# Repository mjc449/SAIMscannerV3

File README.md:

# SAIMscannerV3

Check out the preprint at https://doi.org/10.1101/533349 for more details

This project has been developed in house by the Paszek and Zipfel labs
at Cornell University over a few years and several revisions.  The
primary developer has been Marshall Colville (mjc449@cornell.edu) with
assistance from Warren Zipfel and Matt Paszek.

Given the scope of the project, the multiple revisions and adaptations
that the hardware and software have gone through, and the fact that
we are not electrical or software engineers the code tends to change
styles and not follow typical conventions.  As the project evolves we
intend to bring everything into line with a single, consistent set of
coding guidelines.  However, to go through the entire project will take
some time.  We will publish a set of style guides soon to be used throughout
the project that reflects typical coding conventions.

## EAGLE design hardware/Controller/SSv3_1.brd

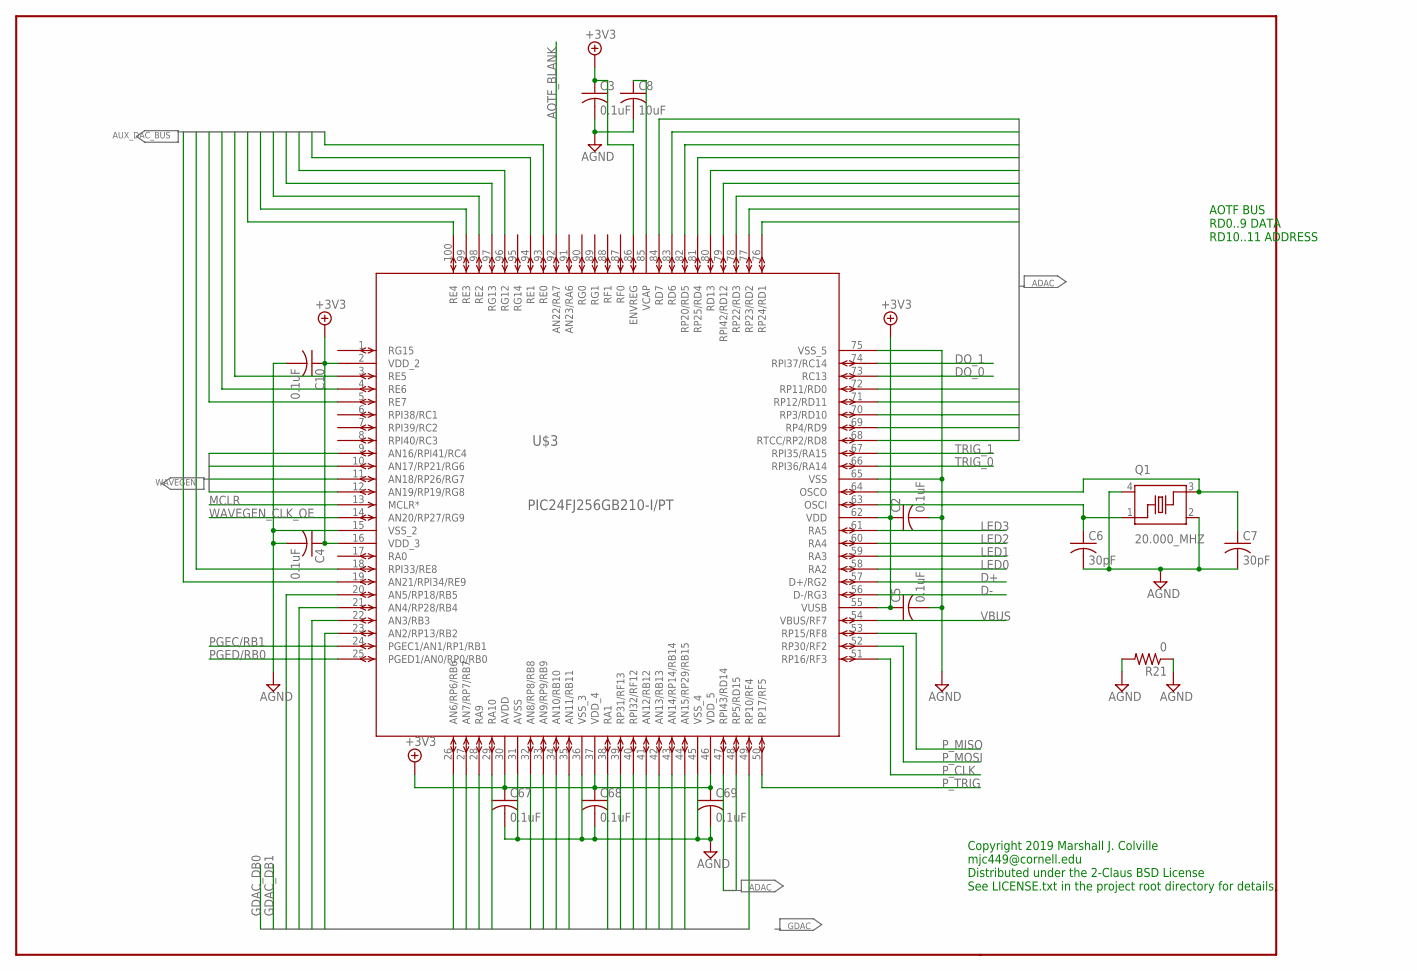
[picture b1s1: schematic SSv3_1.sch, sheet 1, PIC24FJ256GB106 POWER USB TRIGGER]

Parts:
C2, C3, C4, C5, C10, C67, C68, C69: 0.1uF; C0603
C6, C7: 30pF; C0603
C8: 10uF; C0805
Q1: 20.000_MHZ; CTS406
R21: 0; R0603
U$3: PIC24FJ256GB210-I/PT; TQFP100_12X12MC

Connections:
+3V3: C2.1, C3.1, C4.1, C5.1, C10.1, C67.1, C68.1, C69.1, U$3.2 (VDD_2), U$3.16 (VDD_3), U$3.30 (AVDD), U$3.37 (VDD_4), U$3.46 (VDD_5), U$3.55 (VUSB), U$3.62 (VDD), U$3.86 (ENVREG); also elsewhere on the board
ADAC0: U$3.72 (RP11/RD0); also elsewhere on the board
ADAC0_CS: U$3.79 (RPI42/RD12); also elsewhere on the board
ADAC1: U$3.76 (RP24/RD1); also elsewhere on the board
ADAC1_CS: U$3.80 (RD13); also elsewhere on the board
ADAC2: U$3.77 (RP23/RD2); also elsewhere on the board
ADAC3: U$3.78 (RP22/RD3); also elsewhere on the board
ADAC4: U$3.81 (RP25/RD4); also elsewhere on the board
ADAC5: U$3.82 (RP20/RD5); also elsewhere on the board
ADAC6: U$3.83 (RD6); also elsewhere on the board
ADAC7: U$3.84 (RD7); also elsewhere on the board
ADAC8: U$3.68 (RTCC/RP2/RD8); also elsewhere on the board
ADAC9: U$3.69 (RP4/RD9); also elsewhere on the board
ADAC_A0: U$3.70 (RP3/RD10); also elsewhere on the board
ADAC_A1: U$3.71 (RP12/RD11); also elsewhere on the board
ADAC_LOAD: U$3.47 (RPI43/RD14); also elsewhere on the board
ADAC_RS: U$3.48 (RP5/RD15); also elsewhere on the board
AGND: C2.2, C3.2, C4.2, C5.2, C6.2, C7.2, C8.2, C10.2, C67.2, C68.2, C69.2, Q1.2, Q1.4, R21.1, R21.2, U$3.15 (VSS_2), U$3.31 (AVSS), U$3.36 (VSS_3), U$3.45 (VSS_4), U$3.65 (VSS), U$3.75 (VSS_5); also elsewhere on the board
AOTF_BLANK: U$3.92 (AN22/RA7); also elsewhere on the board
AUX_DAC_A/B: U$3.97 (RG13); also elsewhere on the board
AUX_DAC_CS: U$3.96 (RG12); also elsewhere on the board
AUX_DAC_DB0: U$3.93 (RE0); also elsewhere on the board
AUX_DAC_DB1: U$3.94 (RE1); also elsewhere on the board
AUX_DAC_DB2: U$3.98 (RE2); also elsewhere on the board
AUX_DAC_DB3: U$3.99 (RE3); also elsewhere on the board
AUX_DAC_DB4: U$3.100 (RE4); also elsewhere on the board
AUX_DAC_DB5: U$3.3 (RE5); also elsewhere on the board
AUX_DAC_DB6: U$3.4 (RE6); also elsewhere on the board
AUX_DAC_DB7: U$3.5 (RE7); also elsewhere on the board
AUX_DAC_DB8: U$3.18 (RPI33/RE8); also elsewhere on the board
AUX_DAC_DB9: U$3.19 (AN21/RPI34/RE9); also elsewhere on the board
D+: U$3.57 (D+/RG2); also elsewhere on the board
D-: U$3.56 (D-/RG3); also elsewhere on the board
DO_0: U$3.73 (RC13); also elsewhere on the board
DO_1: U$3.74 (RPI37/RC14); also elsewhere on the board
GDAC_A0: U$3.28 (RA9); also elsewhere on the board
GDAC_A1: U$3.29 (RA10); also elsewhere on the board
GDAC_DB2: U$3.23 (AN2/RP13/RB2); also elsewhere on the board
GDAC_DB3: U$3.22 (AN3/RB3); also elsewhere on the board
GDAC_DB4: U$3.21 (AN4/RP28/RB4); also elsewhere on the board
GDAC_DB5: U$3.20 (AN5/RP18/RB5); also elsewhere on the board
GDAC_DB6: U$3.26 (AN6/RP6/RB6); also elsewhere on the board
GDAC_DB7: U$3.27 (AN7/RP7/RB7); also elsewhere on the board
GDAC_DB8: U$3.32 (AN8/RP8/RB8); also elsewhere on the board
GDAC_DB9: U$3.33 (AN9/RP9/RB9); also elsewhere on the board
GDAC_DB10: U$3.34 (AN10/RB10); also elsewhere on the board
GDAC_DB11: U$3.35 (AN11/RB11); also elsewhere on the board
GDAC_DB12: U$3.41 (AN12/RB12); also elsewhere on the board
GDAC_DB13: U$3.42 (AN13/RB13); also elsewhere on the board
GDAC_DB14: U$3.43 (AN14/RP14/RB14); also elsewhere on the board
GDAC_DB15: U$3.44 (AN15/RP29/RB15); also elsewhere on the board
GDAC_LOAD: U$3.40 (RPI32/RF12); also elsewhere on the board
GDAC_RS: U$3.38 (RA1); also elsewhere on the board
LED0: U$3.58 (RA2); also elsewhere on the board
LED1: U$3.59 (RA3); also elsewhere on the board
LED2: U$3.60 (RA4); also elsewhere on the board
LED3: U$3.61 (RA5); also elsewhere on the board
MCLR: U$3.13 (MCLR*); also elsewhere on the board
unnamed: C8.1, U$3.85 (VCAP)
unnamed: C6.1, Q1.1, U$3.63 (OSCI)
unnamed: C7.1, Q1.3, U$3.64 (OSCO)
PGEC/RB1: U$3.24 (PGEC1/AN1/RP1/RB1); also elsewhere on the board
PGED/RB0: U$3.25 (PGED1/AN0/RP0/RB0); also elsewhere on the board
P_CLK: U$3.51 (RP16/RF3); also elsewhere on the board
P_MISO: U$3.53 (RP15/RF8); also elsewhere on the board
P_MOSI: U$3.52 (RP30/RF2); also elsewhere on the board
P_TRIG: U$3.50 (RP17/RF5); also elsewhere on the board
TRIG_0: U$3.66 (RPI36/RA14); also elsewhere on the board
TRIG_1: U$3.67 (RPI35/RA15); also elsewhere on the board
VBUS: U$3.54 (VBUS/RF7); also elsewhere on the board
WAVEGEN_CLK_OE: U$3.14 (AN20/RP27/RG9); also elsewhere on the board
WAVEGEN_SCK: U$3.10 (AN17/RP21/RG6); also elsewhere on the board
WAVEGEN_SYNC: U$3.11 (AN18/RP26/RG7); also elsewhere on the board
X_WAVEGEN_SDI: U$3.9 (AN16/RPI41/RC4); also elsewhere on the board
X_WR: U$3.39 (RP31/RF13); also elsewhere on the board
Y_WAVEGEN_SDI: U$3.12 (AN19/RP19/RG8); also elsewhere on the board
Y_WR: U$3.49 (RP10/RF4); also elsewhere on the board

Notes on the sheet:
AOTF BUS RD0..9 DATA RD10..11 ADDRESS
Copyright 2019 Marshall J. Colville mjc449@cornell.edu Distributed under the 2-Claus BSD License See LICENSE.txt in the project root directory for details

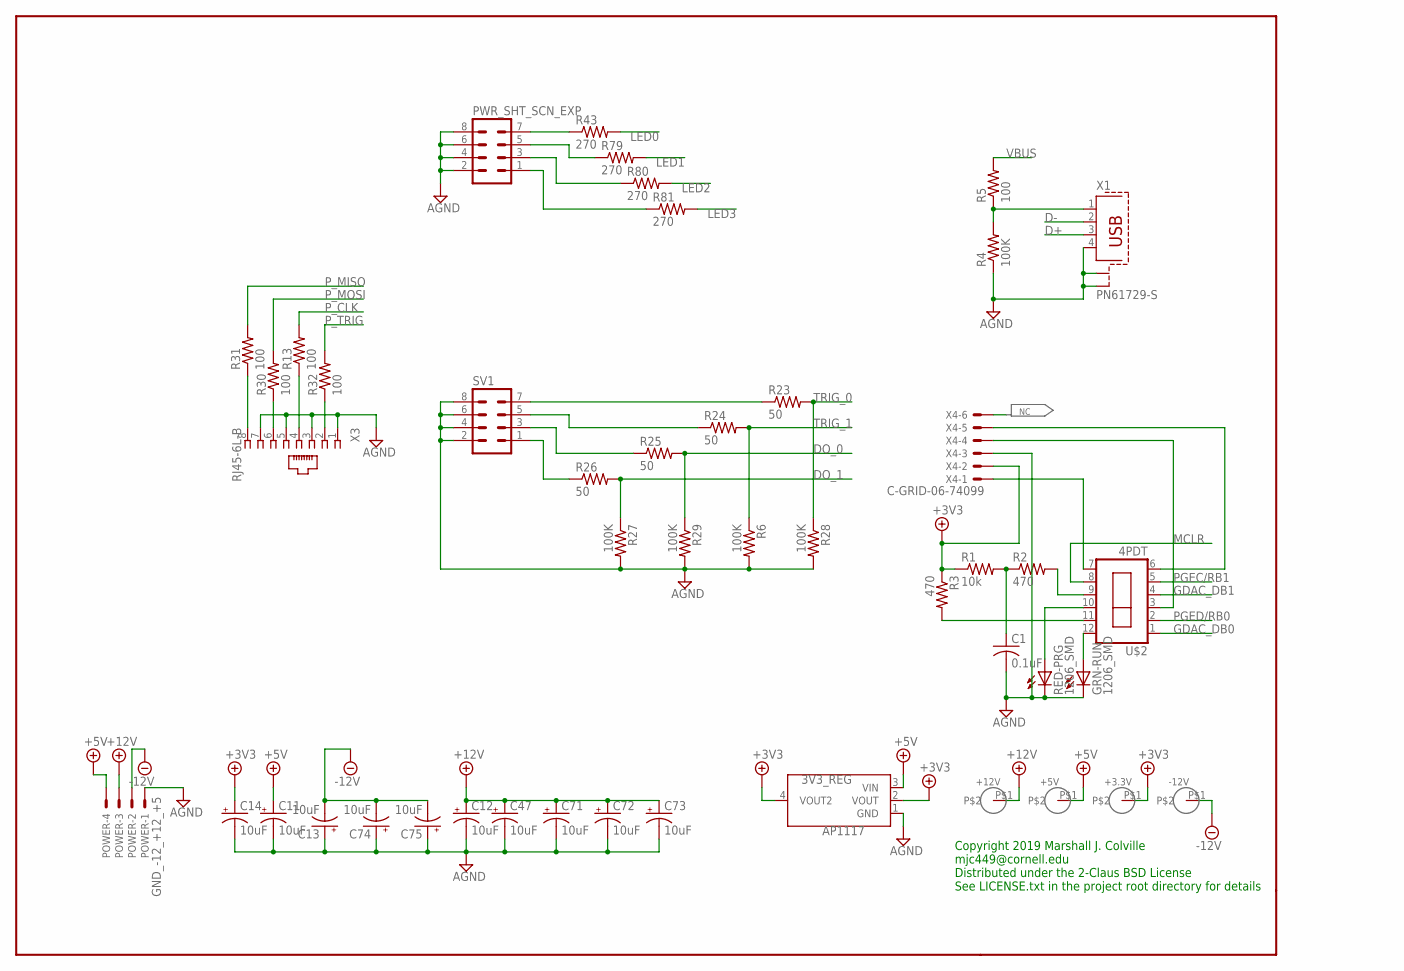
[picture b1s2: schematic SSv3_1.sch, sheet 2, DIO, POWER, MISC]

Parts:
3V3_REG: AP1117; SOT223
+3.3V, +5V, +12V: TESTPOINT
-12V: TESTPOINT
C1: 0.1uF; C0603
C11, C12, C13, C14, C47, C71, C72, C73, C74, C75: 10uF; PANASONIC_B
GRN-RUN: 1206_SMD; LED-1206
POWER: GND_-12_+12_+5; 22-23-2041
PWR_SHT_SCN_EXP: MA04-2
R1: 10k; R0603
R2, R3: 470; R0603
R4, R6, R27, R28, R29: 100K; R0603
R5, R13, R30, R31, R32: 100; R0603
R23, R24, R25, R26: 50; R0603
R43, R79, R80, R81: 270; R0603
RED-PRG: 1206_SMD; LED-1206
SV1: MA04-2
U$2: 4PDT; 4PDT_SMD
X1: PN61729-S
X3: RJ45-6L-B; RJ45-NO-SHIELD
X4: C-GRID-06-74099; 74099-06

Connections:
+3V3: 3V3_REG.2 (VOUT), 3V3_REG.4 (VOUT2), +3.3V.P$1, C14.+, R1.1, R3.1, X4.2; also elsewhere on the board
+5V: 3V3_REG.3 (VIN), +5V.P$1, C11.+, POWER.4; also elsewhere on the board
+12V: +12V.P$1, C12.+, C47.+, C71.+, C72.+, C73.+, POWER.3; also elsewhere on the board
-12V: -12V.P$1, C13.-, C74.-, C75.-, POWER.2; also elsewhere on the board
AGND: 3V3_REG.1 (GND), C1.2, C11.-, C12.-, C13.+, C14.-, C47.-, C71.-, C72.-, C73.-, C74.+, C75.+, GRN-RUN.C, POWER.1, PWR_SHT_SCN_EXP.2, PWR_SHT_SCN_EXP.4, PWR_SHT_SCN_EXP.6, PWR_SHT_SCN_EXP.8, R4.1, R6.2, R27.2, R28.2, R29.2, RED-PRG.C, SV1.2, SV1.4, SV1.6, SV1.8, X1.4, X1.S1, X1.S2, X3.1, X3.3, X3.5, X3.7, X4.3; also elsewhere on the board
D+: X1.3; also elsewhere on the board
D-: X1.2; also elsewhere on the board
DO_0: R25.2, R29.1; also elsewhere on the board
DO_1: R26.2, R27.1; also elsewhere on the board
GDAC_DB0: U$2.1; also elsewhere on the board
GDAC_DB1: U$2.4; also elsewhere on the board
LED0: R43.2; also elsewhere on the board
LED1: R79.2; also elsewhere on the board
LED2: R80.2; also elsewhere on the board
LED3: R81.2; also elsewhere on the board
MCLR: U$2.8; also elsewhere on the board
unnamed: U$2.7, X4.1
unnamed: PWR_SHT_SCN_EXP.7, R43.1
unnamed: R2.2, U$2.9
unnamed: C1.1, R1.2, R2.1
unnamed: R3.2, U$2.11
unnamed: RED-PRG.A, U$2.10
unnamed: GRN-RUN.A, U$2.12
unnamed: R31.1, X3.8
unnamed: R30.1, X3.6
unnamed: PWR_SHT_SCN_EXP.5, R79.1
unnamed: PWR_SHT_SCN_EXP.3, R80.1
unnamed: PWR_SHT_SCN_EXP.1, R81.1
unnamed: R13.1, X3.4
unnamed: R32.1, X3.2
unnamed: R25.1, SV1.3
unnamed: R24.1, SV1.5
unnamed: R23.1, SV1.7
unnamed: R26.1, SV1.1
PGEC: U$2.6, X4.5
PGEC/RB1: U$2.5; also elsewhere on the board
PGED: U$2.3, X4.4
PGED/RB0: U$2.2; also elsewhere on the board
P_CLK: R13.2; also elsewhere on the board
P_MISO: R31.2; also elsewhere on the board
P_MOSI: R30.2; also elsewhere on the board
P_TRIG: R32.2; also elsewhere on the board
TRIG_0: R23.2, R28.1; also elsewhere on the board
TRIG_1: R6.1, R24.2; also elsewhere on the board
USB1: R4.2, R5.1, X1.1
VBUS: R5.2; also elsewhere on the board

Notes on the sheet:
Copyright 2019 Marshall J. Colville mjc449@cornell.edu Distributed under the 2-Claus BSD License See LICENSE.txt in the project root directory for details

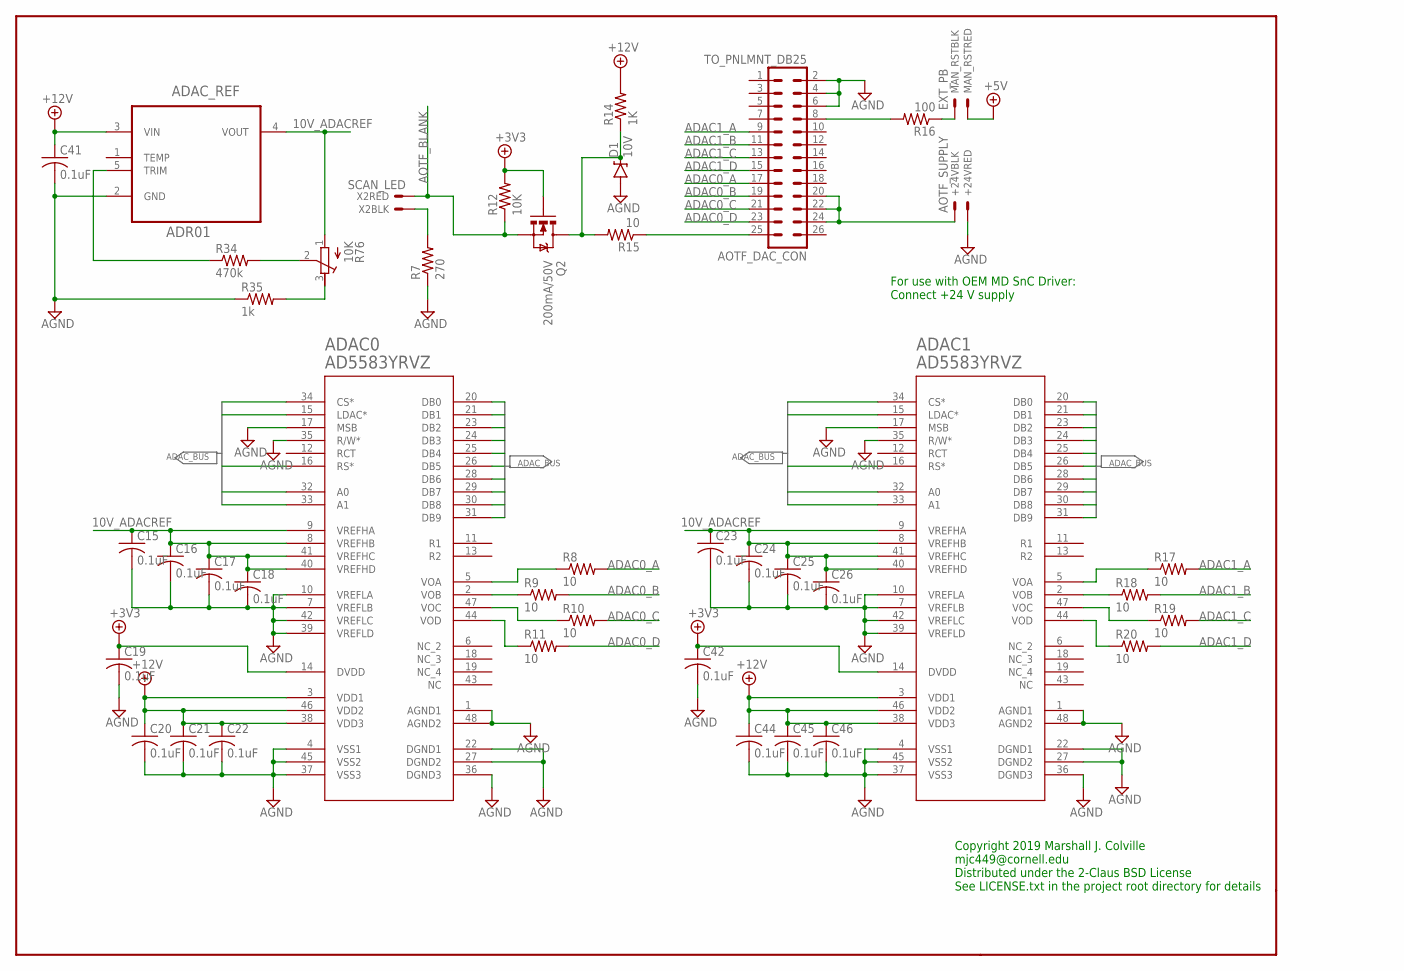
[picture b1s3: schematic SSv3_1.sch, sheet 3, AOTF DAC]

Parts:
+24V: AOTF_SUPPLY; 22-23-2021
ADAC0, ADAC1: AD5583YRVZ; RV_48
ADAC_REF: ADR01; SOT65P210X110-5N
AOTF_DAC_CON: TO_PNLMNT_DB25; ML26
C15, C16, C17, C18, C19, C20, C21, C22, C23, C24, C25, C26, C41, C42, C44, C45, C46: 0.1uF; C0603
D1: 10V; SOD-123
MAN_RST: EXT_PB; 22-23-2021
Q2: 200mA/50V; SOT23-3
R7: 270; R0603
R8, R9, R10, R11, R15, R17, R18, R19, R20: 10; R0603
R12: 10K; R0603
R14: 1K; R0603
R16: 100; R0603
R34: 470k; R0603
R35: 1k; R0603
R76: 10K; RTRIMTS63Y
X2: SCAN_LED; 22-23-2021

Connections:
10V_ADACREF: ADAC0.8 (VREFHB), ADAC0.9 (VREFHA), ADAC0.40 (VREFHD), ADAC0.41 (VREFHC), ADAC1.8 (VREFHB), ADAC1.9 (VREFHA), ADAC1.40 (VREFHD), ADAC1.41 (VREFHC), ADAC_REF.4 (VOUT), C15.1, C16.1, C17.1, C18.1, C23.1, C24.1, C25.1, C26.1, R76.1 (A)
+3V3: ADAC0.14 (DVDD), ADAC1.14 (DVDD), C19.1, C42.1, Q2.1 (G), R12.2; also elsewhere on the board
+5V: MAN_RST.2; also elsewhere on the board
+12V: ADAC0.3 (VDD1), ADAC0.38 (VDD3), ADAC0.46 (VDD2), ADAC1.3 (VDD1), ADAC1.38 (VDD3), ADAC1.46 (VDD2), ADAC_REF.3 (VIN), C20.1, C21.1, C22.1, C41.1, C44.1, C45.1, C46.1, R14.2; also elsewhere on the board
+24V: +24V.1, AOTF_DAC_CON.20, AOTF_DAC_CON.22, AOTF_DAC_CON.24
ADAC0: ADAC0.20 (DB0), ADAC1.20 (DB0); also elsewhere on the board
ADAC0_A: AOTF_DAC_CON.17, R8.2
ADAC0_B: AOTF_DAC_CON.19, R9.2
ADAC0_C: AOTF_DAC_CON.21, R10.2
ADAC0_CS: ADAC0.34 (CS*); also elsewhere on the board
ADAC0_D: AOTF_DAC_CON.23, R11.2
ADAC1: ADAC0.21 (DB1), ADAC1.21 (DB1); also elsewhere on the board
ADAC1_A: AOTF_DAC_CON.9, R17.2
ADAC1_B: AOTF_DAC_CON.11, R18.2
ADAC1_C: AOTF_DAC_CON.13, R19.2
ADAC1_CS: ADAC1.34 (CS*); also elsewhere on the board
ADAC1_D: AOTF_DAC_CON.15, R20.2
ADAC2: ADAC0.23 (DB2), ADAC1.23 (DB2); also elsewhere on the board
ADAC3: ADAC0.24 (DB3), ADAC1.24 (DB3); also elsewhere on the board
ADAC4: ADAC0.25 (DB4), ADAC1.25 (DB4); also elsewhere on the board
ADAC5: ADAC0.26 (DB5), ADAC1.26 (DB5); also elsewhere on the board
ADAC6: ADAC0.28 (DB6), ADAC1.28 (DB6); also elsewhere on the board
ADAC7: ADAC0.29 (DB7), ADAC1.29 (DB7); also elsewhere on the board
ADAC8: ADAC0.30 (DB8), ADAC1.30 (DB8); also elsewhere on the board
ADAC9: ADAC0.31 (DB9), ADAC1.31 (DB9); also elsewhere on the board
ADAC_A0: ADAC0.32 (A0), ADAC1.32 (A0); also elsewhere on the board
ADAC_A1: ADAC0.33 (A1), ADAC1.33 (A1); also elsewhere on the board
ADAC_LOAD: ADAC0.15 (LDAC*), ADAC1.15 (LDAC*); also elsewhere on the board
ADAC_RS: ADAC0.16 (RS*), ADAC1.16 (RS*); also elsewhere on the board
AGND: +24V.2, ADAC0.1 (AGND1), ADAC0.4 (VSS1), ADAC0.7 (VREFLB), ADAC0.10 (VREFLA), ADAC0.17 (MSB), ADAC0.22 (DGND1), ADAC0.27 (DGND2), ADAC0.35 (R/W*), ADAC0.36 (DGND3), ADAC0.37 (VSS3), ADAC0.39 (VREFLD), ADAC0.42 (VREFLC), ADAC0.45 (VSS2), ADAC0.48 (AGND2), ADAC1.1 (AGND1), ADAC1.4 (VSS1), ADAC1.7 (VREFLB), ADAC1.10 (VREFLA), ADAC1.17 (MSB), ADAC1.22 (DGND1), ADAC1.27 (DGND2), ADAC1.35 (R/W*), ADAC1.36 (DGND3), ADAC1.37 (VSS3), ADAC1.39 (VREFLD), ADAC1.42 (VREFLC), ADAC1.45 (VSS2), ADAC1.48 (AGND2), ADAC_REF.2 (GND), AOTF_DAC_CON.2, AOTF_DAC_CON.4, AOTF_DAC_CON.6, C15.2, C16.2, C17.2, C18.2, C19.2, C20.2, C21.2, C22.2, C23.2, C24.2, C25.2, C26.2, C41.2, C42.2, C44.2, C45.2, C46.2, D1.A, R7.1, R35.1; also elsewhere on the board
AOTF_BLANK: Q2.2 (S), R12.1, X2.2; also elsewhere on the board
unnamed: R34.2, R76.2 (S)
unnamed: D1.C, Q2.3 (D), R14.1, R15.2
unnamed: AOTF_DAC_CON.8, R16.2
unnamed: ADAC0.44 (VOD), R11.1
unnamed: ADAC0.47 (VOC), R10.1
unnamed: ADAC0.2 (VOB), R9.1
unnamed: ADAC0.5 (VOA), R8.1
unnamed: ADAC1.5 (VOA), R17.1
unnamed: ADAC1.2 (VOB), R18.1
unnamed: ADAC1.47 (VOC), R19.1
unnamed: ADAC1.44 (VOD), R20.1
unnamed: ADAC_REF.5 (TRIM), R34.1
unnamed: R35.2, R76.3 (E)
unnamed: AOTF_DAC_CON.25, R15.1
unnamed: MAN_RST.1, R16.1
SCAN_LED-: R7.2, X2.1

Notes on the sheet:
For use with OEM MD SnC Driver: Connect +24 V supply
Copyright 2019 Marshall J. Colville mjc449@cornell.edu Distributed under the 2-Claus BSD License See LICENSE.txt in the project root directory for details

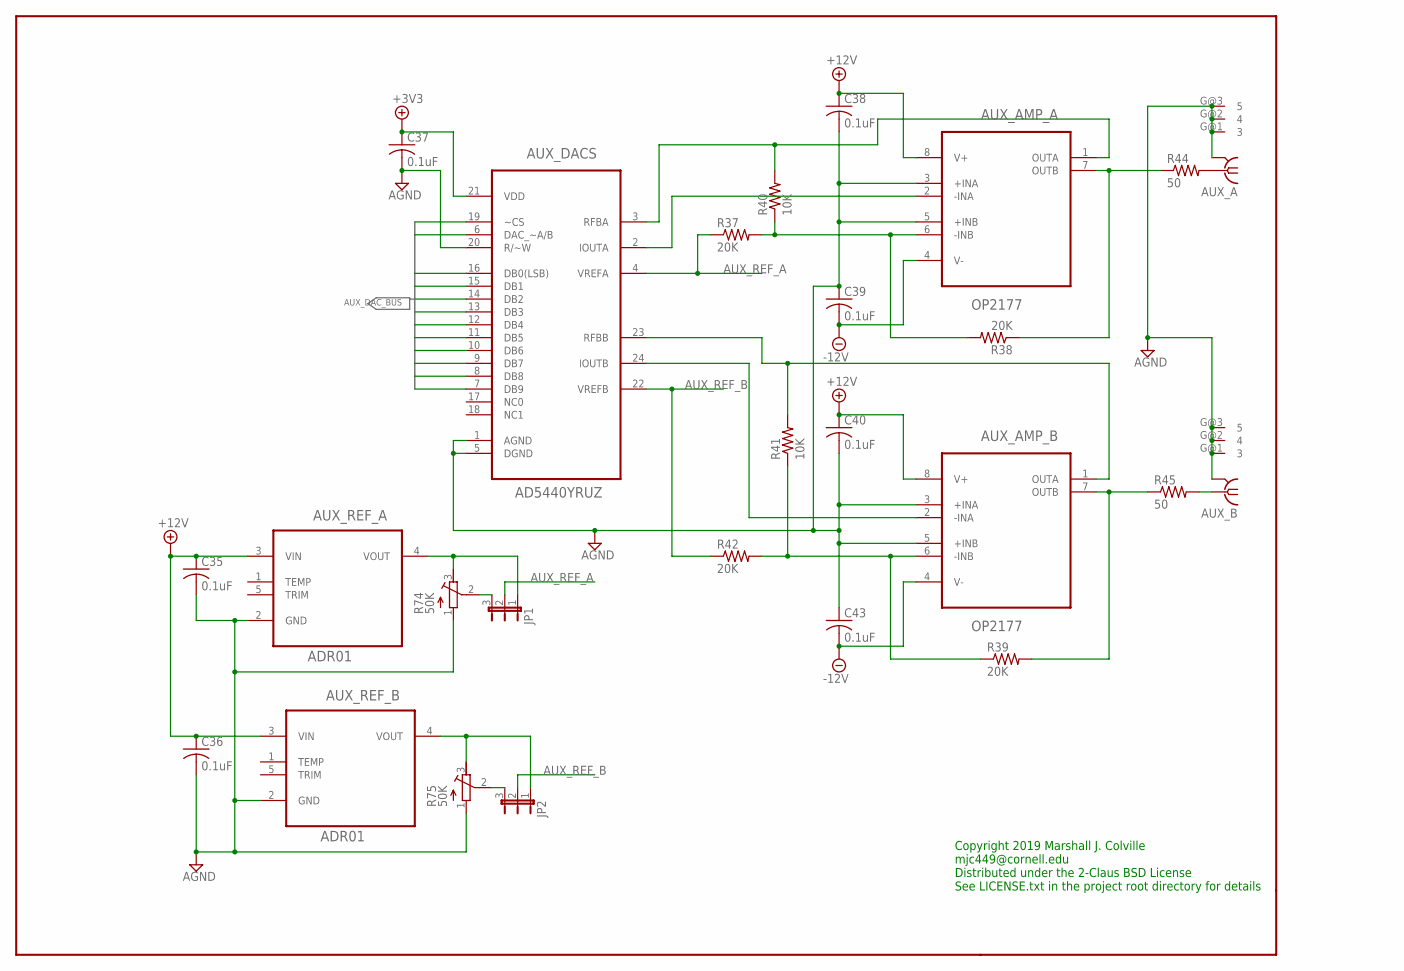
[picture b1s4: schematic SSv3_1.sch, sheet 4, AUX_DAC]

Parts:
AUX_A: SMA_SMT; SIDE_MOUNTSMA
AUX_AMP_A: OP2177; SOP65P490X110-8N
AUX_AMP_B: OP2177; SOP65P490X110-8N
AUX_B: SMA_SMT; SIDE_MOUNTSMA
AUX_DACS: AD5440YRUZ; SOP65P640X120-24N
AUX_REF_A: ADR01; SOT65P210X110-5N
AUX_REF_B: ADR01; SOT65P210X110-5N
C35, C36, C37, C38, C39, C40, C43: 0.1uF; C0603
JP1, JP2: JP2E; JP2
R37, R38, R39, R42: 20K; R0603
R40, R41: 10K; R0603
R44, R45: 50; R0603
R74, R75: 50K; RTRIMTS63Y

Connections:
+3V3: AUX_DACS.21 (VDD), C37.1; also elsewhere on the board
+12V: AUX_AMP_A.8 (V+), AUX_AMP_B.8 (V+), AUX_REF_A.3 (VIN), AUX_REF_B.3 (VIN), C35.1, C36.1, C38.1, C40.1; also elsewhere on the board
-12V: AUX_AMP_A.4 (V-), AUX_AMP_B.4 (V-), C39.2, C43.2; also elsewhere on the board
AGND: AUX_A.G@1 (3), AUX_A.G@2 (4), AUX_A.G@3 (5), AUX_A.G@4 (2), AUX_AMP_A.3 (+INA), AUX_AMP_A.5 (+INB), AUX_AMP_B.3 (+INA), AUX_AMP_B.5 (+INB), AUX_B.G@1 (3), AUX_B.G@2 (4), AUX_B.G@3 (5), AUX_B.G@4 (2), AUX_DACS.1 (AGND), AUX_DACS.5 (DGND), AUX_DACS.20 (R/~W), AUX_REF_A.2 (GND), AUX_REF_B.2 (GND), C35.2, C36.2, C37.2, C38.2, C39.1, C40.2, C43.1, R74.1 (A), R75.1 (A); also elsewhere on the board
AUX_DAC_A/B: AUX_DACS.6 (DAC_~A/B); also elsewhere on the board
AUX_DAC_CS: AUX_DACS.19 (~CS); also elsewhere on the board
AUX_DAC_DB0: AUX_DACS.16 (DB0(LSB)); also elsewhere on the board
AUX_DAC_DB1: AUX_DACS.15 (DB1); also elsewhere on the board
AUX_DAC_DB2: AUX_DACS.14 (DB2); also elsewhere on the board
AUX_DAC_DB3: AUX_DACS.13 (DB3); also elsewhere on the board
AUX_DAC_DB4: AUX_DACS.12 (DB4); also elsewhere on the board
AUX_DAC_DB5: AUX_DACS.11 (DB5); also elsewhere on the board
AUX_DAC_DB6: AUX_DACS.10 (DB6); also elsewhere on the board
AUX_DAC_DB7: AUX_DACS.9 (DB7); also elsewhere on the board
AUX_DAC_DB8: AUX_DACS.8 (DB8); also elsewhere on the board
AUX_DAC_DB9: AUX_DACS.7 (DB9); also elsewhere on the board
AUX_REF_A: AUX_DACS.4 (VREFA), JP1.2, R37.1
AUX_REF_B: AUX_DACS.22 (VREFB), JP2.2, R42.1
unnamed: AUX_REF_B.4 (VOUT), JP2.1, R75.3 (E)
unnamed: AUX_AMP_A.2 (-INA), AUX_DACS.2 (IOUTA)
unnamed: AUX_AMP_A.1 (OUTA), AUX_DACS.3 (RFBA), R40.2
unnamed: JP1.3, R74.2 (S)
unnamed: AUX_REF_A.4 (VOUT), JP1.1, R74.3 (E)
unnamed: AUX_AMP_A.6 (-INB), R37.2, R38.2, R40.1
unnamed: AUX_AMP_B.2 (-INA), AUX_DACS.24 (IOUTB)
unnamed: AUX_AMP_A.7 (OUTB), R38.1, R44.1
unnamed: AUX_AMP_B.1 (OUTA), AUX_DACS.23 (RFBB), R41.2
unnamed: AUX_A.1, R44.2
unnamed: AUX_AMP_B.6 (-INB), R39.1, R41.1, R42.2
unnamed: AUX_B.1, R45.2
unnamed: AUX_AMP_B.7 (OUTB), R39.2, R45.1
unnamed: JP2.3, R75.2 (S)

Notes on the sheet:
Copyright 2019 Marshall J. Colville mjc449@cornell.edu Distributed under the 2-Claus BSD License See LICENSE.txt in the project root directory for details

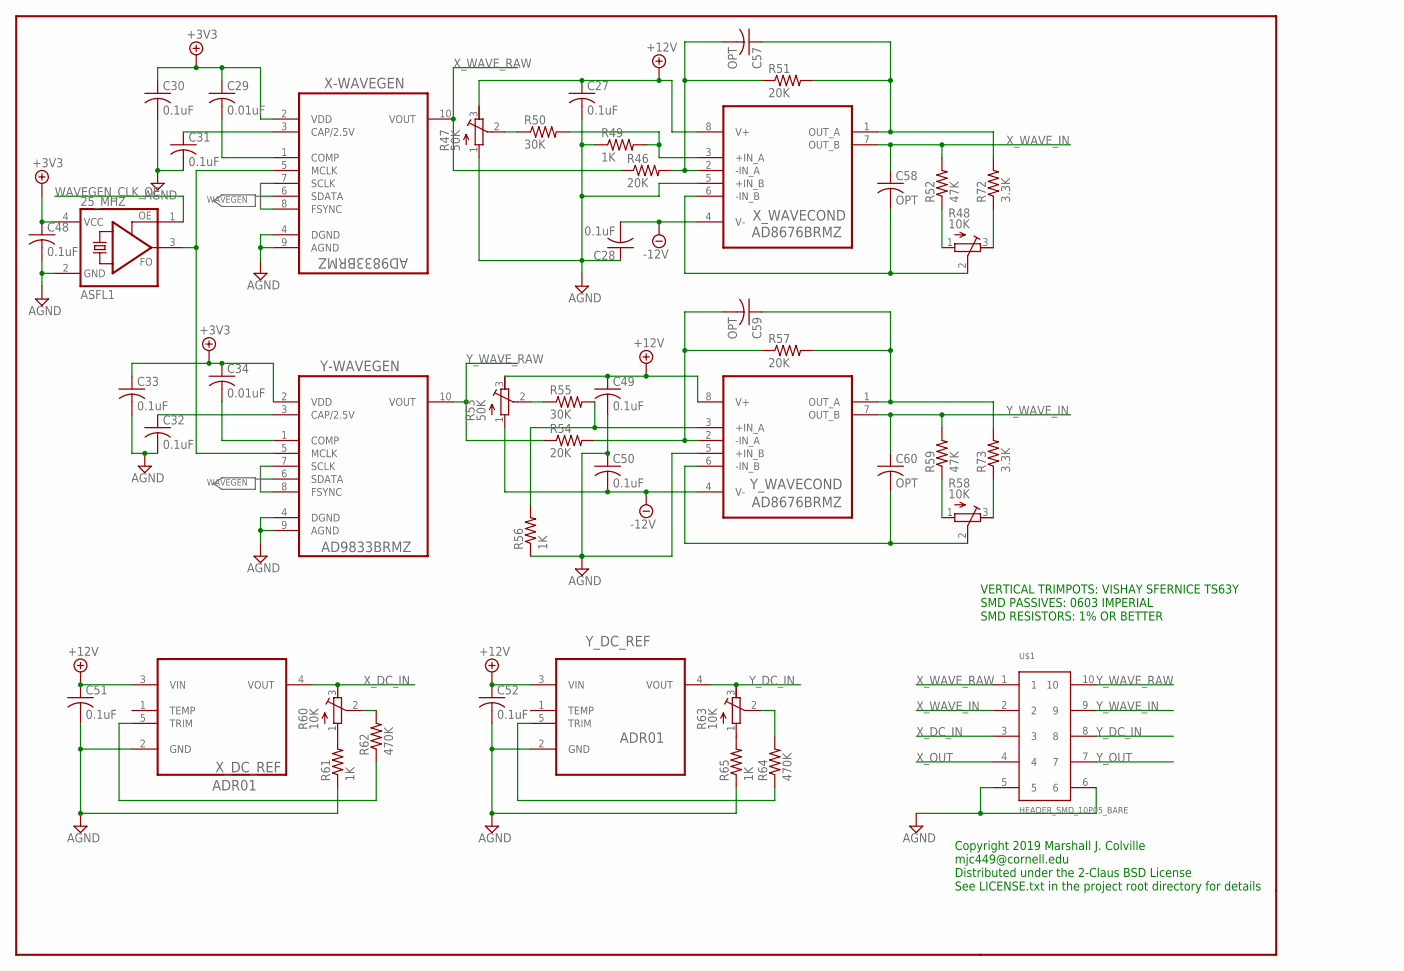
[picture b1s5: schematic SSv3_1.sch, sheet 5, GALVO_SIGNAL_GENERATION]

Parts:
25_MHZ: ASFL1; ASF
C27, C28, C30, C31, C32, C33, C48, C49, C50, C51, C52: 0.1uF; C0603
C29, C34: 0.01uF; C0603
C57, C58, C59, C60: OPT; C0603
R46, R51, R54, R57: 20K; R0603
R47, R53: 50K; RTRIMTS63Y
R48, R58, R60, R63: 10K; RTRIMTS63Y
R49, R56, R61, R65: 1K; R0603
R50, R55: 30K; R0603
R52, R59: 47K; R0603
R62, R64: 470K; R0603
R72, R73: 3.3K; R0603
U$1: HEADER_SMD_10P05_BARE; SMD_HEADER_10P05_BARE
X-WAVEGEN: AD9833BRMZ; SOP50P490X110-10N
X_DC_REF: ADR01; SOT65P210X110-5N
X_WAVECOND: AD8676BRMZ; SOP65P490X110-8N
Y-WAVEGEN: AD9833BRMZ; SOP50P490X110-10N
Y_DC_REF: ADR01; SOT65P210X110-5N
Y_WAVECOND: AD8676BRMZ; SOP65P490X110-8N

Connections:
+3V3: 25_MHZ.4 (VCC), C29.1, C30.1, C33.1, C34.1, C48.1, X-WAVEGEN.2 (VDD), Y-WAVEGEN.2 (VDD); also elsewhere on the board
+12V: C27.1, C49.1, C51.1, C52.1, R47.3 (E), R53.3 (E), X_DC_REF.3 (VIN), X_WAVECOND.8 (V+), Y_DC_REF.3 (VIN), Y_WAVECOND.8 (V+); also elsewhere on the board
-12V: C28.2, C50.2, R53.1 (A), X_WAVECOND.4 (V-), Y_WAVECOND.4 (V-); also elsewhere on the board
AGND: 25_MHZ.2 (GND), C27.2, C28.1, C30.2, C31.2, C32.2, C33.2, C48.2, C49.2, C50.1, C51.2, C52.2, R47.1 (A), R49.1, R56.1, R61.1, R65.1, U$1.5, U$1.6, X-WAVEGEN.4 (DGND), X-WAVEGEN.9 (AGND), X_DC_REF.2 (GND), X_WAVECOND.5 (+IN_B), Y-WAVEGEN.4 (DGND), Y-WAVEGEN.9 (AGND), Y_DC_REF.2 (GND), Y_WAVECOND.5 (+IN_B); also elsewhere on the board
unnamed: 25_MHZ.3 (FO), X-WAVEGEN.5 (MCLK), Y-WAVEGEN.5 (MCLK)
unnamed: C29.2, X-WAVEGEN.1 (COMP)
unnamed: C31.1, X-WAVEGEN.3 (CAP/2.5V)
unnamed: C57.2, R46.2, R51.1, X_WAVECOND.2 (-IN_A)
unnamed: R49.2, R50.2, X_WAVECOND.3 (+IN_A)
unnamed: C32.1, Y-WAVEGEN.3 (CAP/2.5V)
unnamed: C59.1, R57.2, R73.2, Y_WAVECOND.1 (OUT_A)
unnamed: R47.2 (S), R50.1
unnamed: R48.3 (E), R72.1
unnamed: C57.1, R51.2, R72.2, X_WAVECOND.1 (OUT_A)
unnamed: R63.1 (A), R65.2
unnamed: R48.1 (A), R52.1
unnamed: C34.2, Y-WAVEGEN.1 (COMP)
unnamed: C58.2, R48.2 (S), X_WAVECOND.6 (-IN_B)
unnamed: C59.2, R54.2, R57.1, Y_WAVECOND.2 (-IN_A)
unnamed: R55.2, R56.2, Y_WAVECOND.3 (+IN_A)
unnamed: R53.2 (S), R55.1
unnamed: C60.2, R58.2 (S), Y_WAVECOND.6 (-IN_B)
unnamed: R60.1 (A), R61.2
unnamed: R58.1 (A), R59.1
unnamed: R60.2 (S), R62.2
unnamed: R62.1, X_DC_REF.5 (TRIM)
unnamed: R63.2 (S), R64.2
unnamed: R64.1, Y_DC_REF.5 (TRIM)
unnamed: R58.3 (E), R73.1
WAVEGEN_CLK_OE: 25_MHZ.1 (OE); also elsewhere on the board
WAVEGEN_SCK: X-WAVEGEN.7 (SCLK), Y-WAVEGEN.7 (SCLK); also elsewhere on the board
WAVEGEN_SYNC: X-WAVEGEN.8 (FSYNC), Y-WAVEGEN.8 (FSYNC); also elsewhere on the board
X_DC_IN: R60.3 (E), U$1.3, X_DC_REF.4 (VOUT); also elsewhere on the board
X_OUT: U$1.4; also elsewhere on the board
X_WAVEGEN_SDI: X-WAVEGEN.6 (SDATA); also elsewhere on the board
X_WAVE_IN: C58.1, R52.2, U$1.2, X_WAVECOND.7 (OUT_B); also elsewhere on the board
X_WAVE_RAW: R46.1, U$1.1, X-WAVEGEN.10 (VOUT)
Y_DC_IN: R63.3 (E), U$1.8, Y_DC_REF.4 (VOUT); also elsewhere on the board
Y_OUT: U$1.7; also elsewhere on the board
Y_WAVEGEN_SDI: Y-WAVEGEN.6 (SDATA); also elsewhere on the board
Y_WAVE_IN: C60.1, R59.2, U$1.9, Y_WAVECOND.7 (OUT_B); also elsewhere on the board
Y_WAVE_RAW: R54.1, U$1.10, Y-WAVEGEN.10 (VOUT)

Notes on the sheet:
VERTICAL TRIMPOTS: VISHAY SFERNICE TS63Y SMD PASSIVES: 0603 IMPERIAL SMD RESISTORS: 1% OR BETTER
Copyright 2019 Marshall J. Colville mjc449@cornell.edu Distributed under the 2-Claus BSD License See LICENSE.txt in the project root directory for details

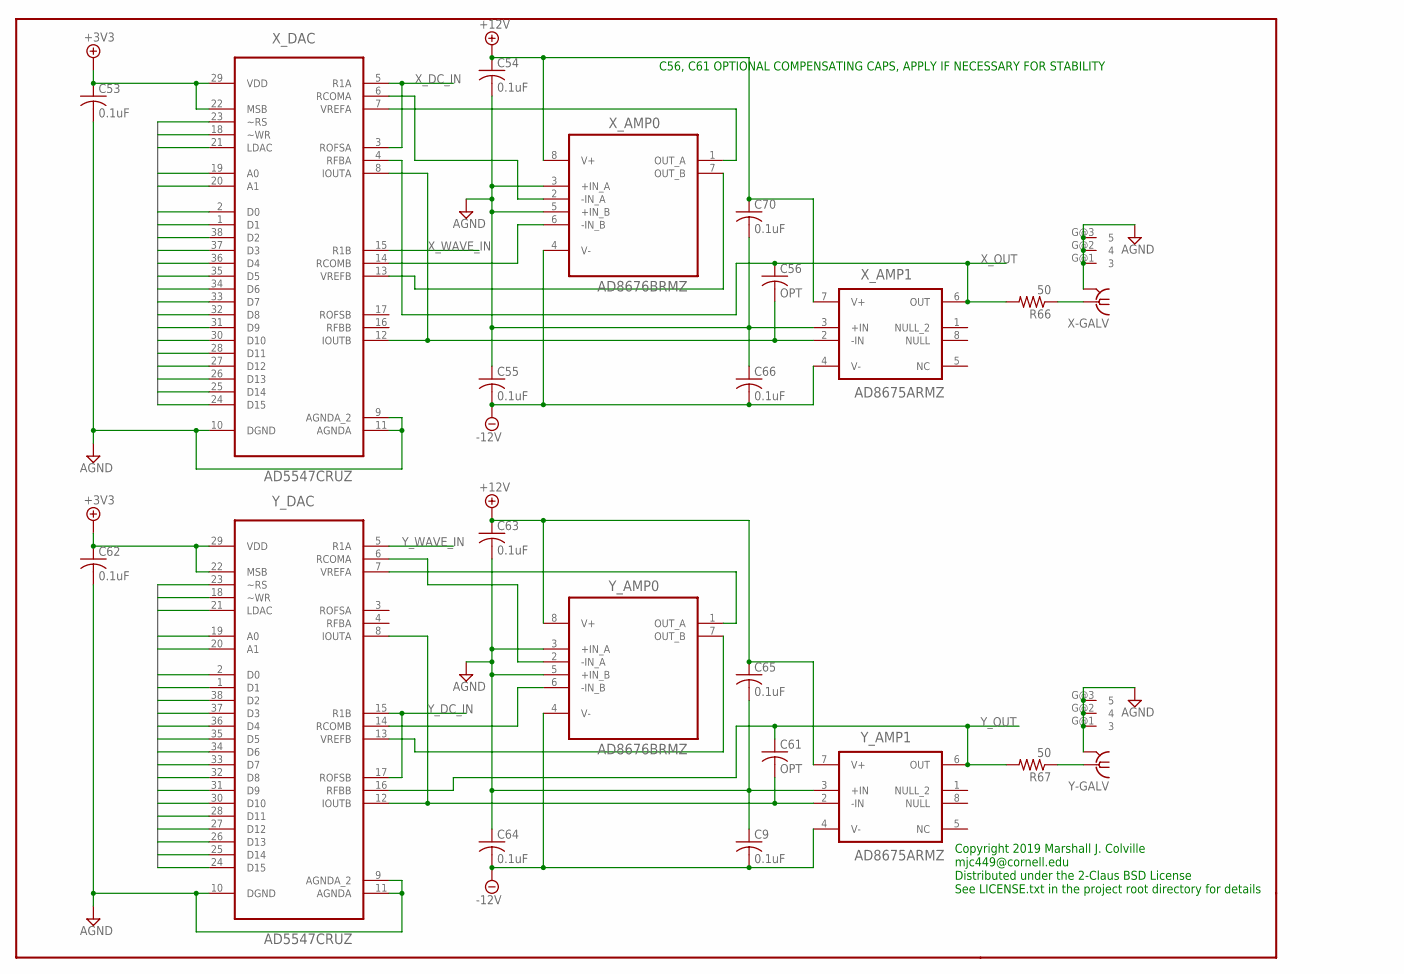
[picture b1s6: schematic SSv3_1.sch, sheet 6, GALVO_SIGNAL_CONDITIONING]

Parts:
C9, C53, C54, C55, C62, C63, C64, C65, C66, C70: 0.1uF; C0603
C56, C61: OPT; C0603
R66, R67: 50; R0603
X-GALV: SMA_SMT; SIDE_MOUNTSMA
X_AMP0: AD8676BRMZ; SOP65P490X110-8N
X_AMP1: AD8675ARMZ; SOP65P490X110-8N
X_DAC: AD5547CRUZ; SOP50P640X120-38N
Y-GALV: SMA_SMT; SIDE_MOUNTSMA
Y_AMP0: AD8676BRMZ; SOP65P490X110-8N
Y_AMP1: AD8675ARMZ; SOP65P490X110-8N
Y_DAC: AD5547CRUZ; SOP50P640X120-38N

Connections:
+3V3: C53.1, C62.1, X_DAC.22 (MSB), X_DAC.29 (VDD), Y_DAC.22 (MSB), Y_DAC.29 (VDD); also elsewhere on the board
+12V: C54.1, C63.1, C65.1, C70.1, X_AMP0.8 (V+), X_AMP1.7 (V+), Y_AMP0.8 (V+), Y_AMP1.7 (V+); also elsewhere on the board
-12V: C9.2, C55.2, C64.2, C66.2, X_AMP0.4 (V-), X_AMP1.4 (V-), Y_AMP0.4 (V-), Y_AMP1.4 (V-); also elsewhere on the board
AGND: C9.1, C53.2, C54.2, C55.1, C62.2, C63.2, C64.1, C65.2, C66.1, C70.2, X-GALV.G@1 (3), X-GALV.G@2 (4), X-GALV.G@3 (5), X-GALV.G@4 (2), X_AMP0.3 (+IN_A), X_AMP0.5 (+IN_B), X_AMP1.3 (+IN), X_DAC.9 (AGNDA_2), X_DAC.10 (DGND), X_DAC.11 (AGNDA), Y-GALV.G@1 (3), Y-GALV.G@2 (4), Y-GALV.G@3 (5), Y-GALV.G@4 (2), Y_AMP0.3 (+IN_A), Y_AMP0.5 (+IN_B), Y_AMP1.3 (+IN), Y_DAC.9 (AGNDA_2), Y_DAC.10 (DGND), Y_DAC.11 (AGNDA); also elsewhere on the board
GDAC_A0: X_DAC.19 (A0), Y_DAC.19 (A0); also elsewhere on the board
GDAC_A1: X_DAC.20 (A1), Y_DAC.20 (A1); also elsewhere on the board
GDAC_DB0: X_DAC.2 (D0), Y_DAC.2 (D0); also elsewhere on the board
GDAC_DB1: X_DAC.1 (D1), Y_DAC.1 (D1); also elsewhere on the board
GDAC_DB2: X_DAC.38 (D2), Y_DAC.38 (D2); also elsewhere on the board
GDAC_DB3: X_DAC.37 (D3), Y_DAC.37 (D3); also elsewhere on the board
GDAC_DB4: X_DAC.36 (D4), Y_DAC.36 (D4); also elsewhere on the board
GDAC_DB5: X_DAC.35 (D5), Y_DAC.35 (D5); also elsewhere on the board
GDAC_DB6: X_DAC.34 (D6), Y_DAC.34 (D6); also elsewhere on the board
GDAC_DB7: X_DAC.33 (D7), Y_DAC.33 (D7); also elsewhere on the board
GDAC_DB8: X_DAC.32 (D8), Y_DAC.32 (D8); also elsewhere on the board
GDAC_DB9: X_DAC.31 (D9), Y_DAC.31 (D9); also elsewhere on the board
GDAC_DB10: X_DAC.30 (D10), Y_DAC.30 (D10); also elsewhere on the board
GDAC_DB11: X_DAC.28 (D11), Y_DAC.28 (D11); also elsewhere on the board
GDAC_DB12: X_DAC.27 (D12), Y_DAC.27 (D12); also elsewhere on the board
GDAC_DB13: X_DAC.26 (D13), Y_DAC.26 (D13); also elsewhere on the board
GDAC_DB14: X_DAC.25 (D14), Y_DAC.25 (D14); also elsewhere on the board
GDAC_DB15: X_DAC.24 (D15), Y_DAC.24 (D15); also elsewhere on the board
GDAC_LOAD: X_DAC.21 (LDAC), Y_DAC.21 (LDAC); also elsewhere on the board
GDAC_RS: X_DAC.23 (~RS), Y_DAC.23 (~RS); also elsewhere on the board
unnamed: Y_AMP0.2 (-IN_A), Y_DAC.6 (RCOMA)
unnamed: X_AMP0.6 (-IN_B), X_DAC.14 (RCOMB)
unnamed: Y_AMP0.1 (OUT_A), Y_DAC.7 (VREFA)
unnamed: Y_AMP0.7 (OUT_B), Y_DAC.13 (VREFB)
unnamed: R66.1, X-GALV.1
unnamed: X_AMP0.2 (-IN_A), X_DAC.6 (RCOMA)
unnamed: R67.1, Y-GALV.1
unnamed: X_AMP0.7 (OUT_B), X_DAC.13 (VREFB)
unnamed: C61.2, Y_AMP1.2 (-IN), Y_DAC.8 (IOUTA), Y_DAC.12 (IOUTB)
unnamed: Y_AMP0.6 (-IN_B), Y_DAC.14 (RCOMB)
unnamed: X_AMP0.1 (OUT_A), X_DAC.7 (VREFA)
unnamed: C56.2, X_AMP1.2 (-IN), X_DAC.8 (IOUTA), X_DAC.12 (IOUTB)
X_DC_IN: X_DAC.3 (ROFSA), X_DAC.5 (R1A); also elsewhere on the board
X_OUT: C56.1, R66.2, X_AMP1.6 (OUT), X_DAC.4 (RFBA); also elsewhere on the board
X_WAVE_IN: X_DAC.15 (R1B); also elsewhere on the board
X_WR: X_DAC.18 (~WR); also elsewhere on the board
Y_DC_IN: Y_DAC.15 (R1B), Y_DAC.17 (ROFSB); also elsewhere on the board
Y_OUT: C61.1, R67.2, Y_AMP1.6 (OUT), Y_DAC.16 (RFBB); also elsewhere on the board
Y_WAVE_IN: Y_DAC.5 (R1A); also elsewhere on the board
Y_WR: Y_DAC.18 (~WR); also elsewhere on the board

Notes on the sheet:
C56, C61 OPTIONAL COMPENSATING CAPS, APPLY IF NECESSARY FOR STABILITY
Copyright 2019 Marshall J. Colville mjc449@cornell.edu Distributed under the 2-Claus BSD License See LICENSE.txt in the project root directory for details

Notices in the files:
parts and their libraries:
SparkFun-DiscreteSemi: Licensing: Creative Commons ShareAlike 4.0 International - https://creativecommons.org/licenses/by-sa/4.0
